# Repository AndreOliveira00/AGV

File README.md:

# AGV
 Automated Guided Vehicle Controlled by Atmega328P

Este repositório contém o relatório do projeto desenvolvido na Licenciatura de Engenharia Eletrotécnica e de Computadores na Unidade curricular LABSI. 
Imagens ilustrativas da PCB final e o desenvolvimento associado.

<b>OBJETIVOS DO PROJETO:</b>
<ul>
<li>Controlo do movimento do veículo, estabelecendo velocidade e sentido de rotação de 2 motores DC;</li>
<li>Processamento dos dados obtidos por um sensor de proximidade ultrassónico de forma a definir o movimento do carro;</li>
<li>Implementação do projeto segundo a orientação do microcontrolador ATMega328P;</li>
<li>Desenvolvimento de toda a programação C assim como desenho das PCB necessárias á execução do projeto;</li>
</ul>

Para outros esclarecimentos contacte pelo email 1181045@isep.ipp.pt.

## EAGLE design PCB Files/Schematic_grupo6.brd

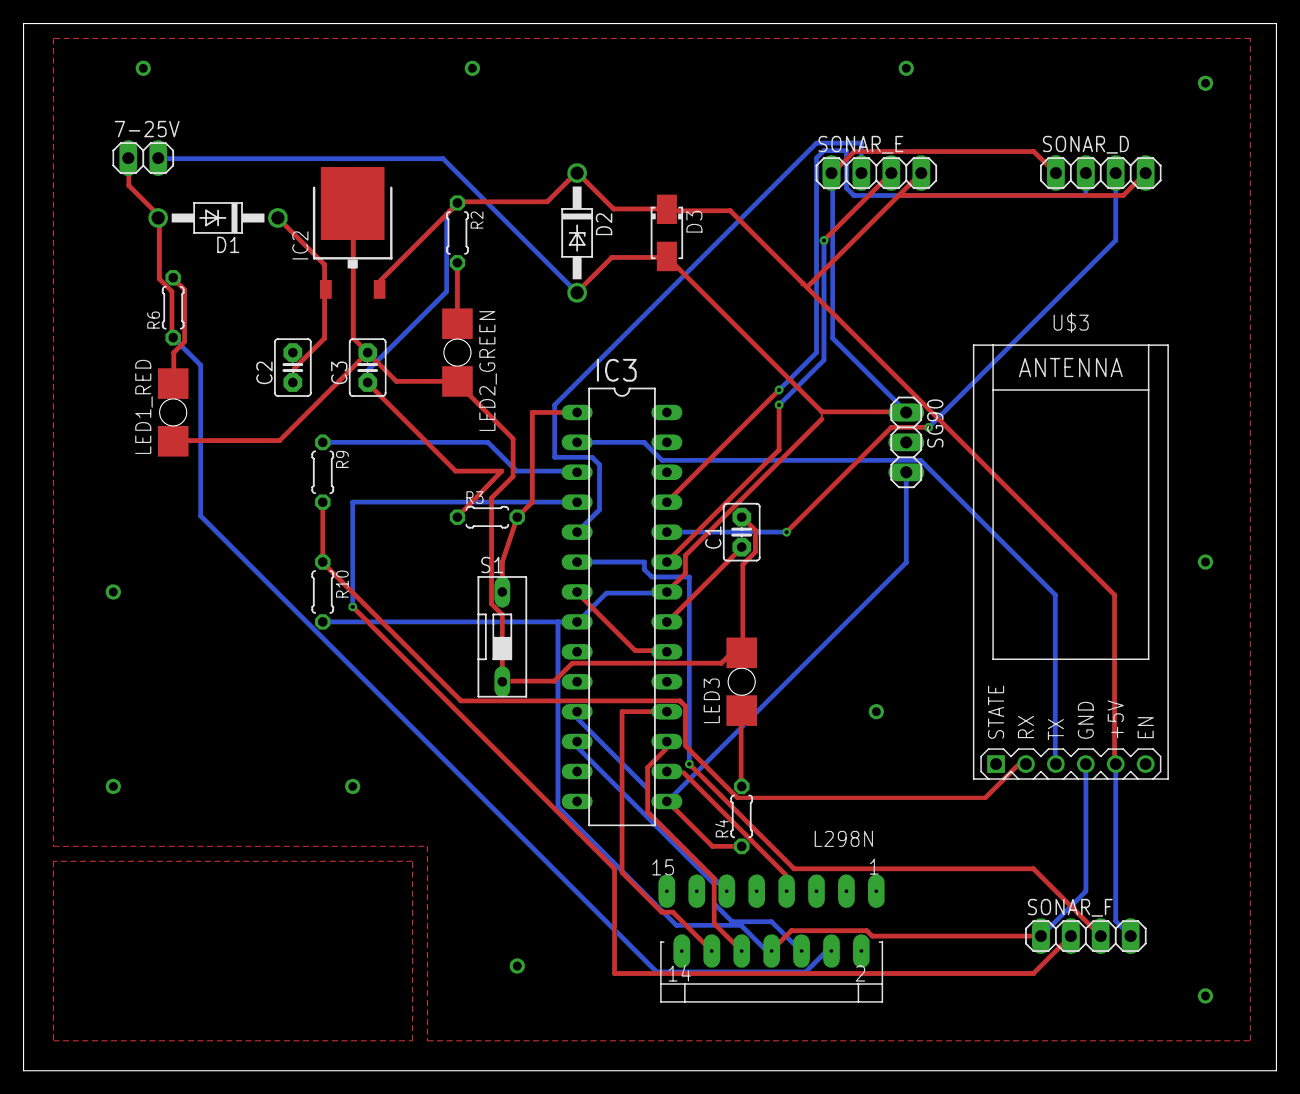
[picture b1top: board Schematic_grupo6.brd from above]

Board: 2 copper layers, 106.3 x 88.9 mm, 25 parts (0 on the bottom side), 26 nets.

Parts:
7-25V: 1X02
C1: 22pF; C2.5-3
C2: 330nF; C2.5-3
C3: 100nF; C2.5-3
D1: 1N4007; DO41-10
D2: 1N4728; DO41Z10
D3: SMAJ5.0A; DO214AC
IC2: LM 7805; TO252
IC3: ATMEGA328P; DIL28-3
L298N: MW-15
LED1_RED, LED2_GREEN, LED3: LAP4-BOTTOM; P47F-BOTTOM
R2, R4: 300; 0204/5
R3: 10k; 0204/5
R6: 2.2k; 0204/5
R9: 1k; 0204/5
R10: 2k; 0204/5
S1: DS-01
SG90: 1X03
SONAR_D: 1X04
SONAR_E: 1X04
SONAR_F: 1X04
U$3: WIRELESS-BLUETOOTH-HC-05

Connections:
0: C1.2, C3.2, IC2.3, LED1_RED.A, LED2_GREEN.C, LED3.C, S1.1
7-25V: 7-25V.1, D1.A, L298N.4, R6.1
.: C3.1, D2.C, D3.C, IC2.2, R2.1, R3.1, SONAR_D.4, SONAR_E.4, SONAR_F.4, U$3.5
AREF: C1.1, IC3.21
AVCC: IC3.7, IC3.20
GND: 7-25V.2, D2.A, D3.A, IC3.8, IC3.22, L298N.8, R10.2, SG90.1, SONAR_D.1, SONAR_E.1, SONAR_F.1, U$3.4
unnamed: LED3.A, R4.2
unnamed: LED1_RED.C, R6.2
unnamed: C2.1, D1.C, IC2.1
unnamed: LED2_GREEN.A, R2.2
PB1: IC3.15, R4.1, SG90.3
PB2: IC3.16, L298N.7
PB3: IC3.17, L298N.10
PC0: IC3.23, SONAR_E.3
PC1: IC3.24, SONAR_D.3
PC2: IC3.25, SONAR_D.2
PD0: IC3.2, U$3.3
PD1: IC3.3, R9.1
PD1': R9.2, R10.1, U$3.2
PD2: IC3.4, SONAR_F.2
PD3: IC3.5, SONAR_E.2
PD4: IC3.6, SONAR_F.3
PD5: IC3.11, L298N.11
PD6: IC3.12, L298N.6
RESET: IC3.1, R3.2, S1.2
S$1: IC3.18, L298N.12

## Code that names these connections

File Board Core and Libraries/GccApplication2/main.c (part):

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
void init(void)
{
	DDRD  = 0b11110010;			// Definir PD6 e PD5 como saída	(OC0A=ENA(motorA) e OC0B=ENB(motorB) respetivamente) PD4(Trig saída frente) PD2(Eco entrada) PD7 (saída IN3) PD2 (INT0) PD3 (INT1) PD1(RX0)
 	PORTD = 0b00000000;			// Inicializar OC0A e OC0B
	
	DDRB  = 0b00110111;			// Definir pino 0,1,2,4 e 5 do PORTB como saída	(LED 1Hz, PWM, IN2, IN4 e IN1 respetivamente)
	PORTB = 0b11001000;			// Inicializar OC0A e ligar pull-ups nas entradas não utilizadas
	
	DDRC  = 0b00000011;			// 2 Sonares atrás PC0 e PC1(Trig saída) PC2(Eco entrada)
	PORTC = 0b11111100;
	
	// TIMER0 para os Motores e Led
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	}
}

void motores()  // PB1 PB2 PB3 PB4
{
	switch (dir)
	{
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void triggersonar(){
	//for (int d = 0; d < 5; ++d)
	//{
	PORTD |= (1<<PD4);					// Ativa trigger
	cont_10us=0;						// Cada definição a zero gasta 2 ciclos de clock = 2us
	cont_10us=0;
	cont_10us=0;
	tempo=0;							// Inicializar variaveis temporais
	tempfim=0;
	tempinit=0;
	PORTD &= (~(1<<PD4));				// Desativa trigger
	flag=1;
	while(flag!=0){};					// Obtive valor novo de dist
	if ((dist<1) || (dist>400)) dist = 400;	// Limite lógico definido para o sonar
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}

void scan_e(){				// Ativar trigger sonar traseiro esquerda
	PORTC |= (1<<PC0);
	cont_10us=0;						// Cada definição a zero gasta 2 ciclos de clock = 2us
	cont_10us=0;
	cont_10us=0;
	cont_10us=0;						// Inicializar variaveis temporais para garantir pelo menos 10 us
	cont_10us=0;
	cont_10us=0;
	PORTC &= (~(1<<PC0));				// Desativa trigger
	while(flag_t==0){};
	//EICRA|= (1<<ISC11) | (1<<ISC10);	// Subida do sinal gera interrupção (INT1)
	flag_t=0;
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
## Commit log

2022-01-03 video

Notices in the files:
parts and their libraries:
diy-modules: Released under the Creative Commons Attribution 4.0 International License: http://creativecommons.org/licenses/by/4.0
